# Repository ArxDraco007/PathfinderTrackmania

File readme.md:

## Building a custom wireless TrackMania controller from scratch.

## Why did I make this project?
I started this as a cool starter project to test my understanding of hardware and electronics.
I wanted to make a controller solely dedicated to a game that is customizable and fully functional with the game. I chose TrackMania, it stuck to my heart, and I made this controller.
It is a split controller to make it ergonomic and handleable to play.

## Why does my project do?
It has movement and custom buttons, such as ak40, ak60, and ak80, which, when placed in calculated best locations, provide digital steering. On a keyboard, your keys are either "on" (100% steering) or "off" (0%). However, at high speeds or on certain surfaces, 100% steering can cause the car to slide out, lose grip, or slow down. Action Keys act like a limiter or a "virtual steering wheel" that holds the wheels at a precise angle.

## Zine - 

## PICTURES - 

## Assembly Instructions?
Heat-press the brass inserts into the case and glue the magnets into place.
Screw the stabilizers into the PCB and mount the sliding switch to the case.
Solder the diodes and header pins to the Seeeduino and PCB.
Click switches into the plate, screw the plate to the case, and add keycaps.
Flash your ZMK firmware to the Seeeduino.
Repeat for the second half, pair them, and test your work.

## How to use it?
Just look at the control buttons and start playing! The WASD keys are on the left of the board, which correspond to the gas, left, brake, and right. The checkpoint and the reset buttons are below, and the AK40, AK60, and AK80 buttons, which control the full speed to 40, 60, and 80 percent. The AK60 is on the left. The AK40 and AK80 are on the right.

### BOM

| Name               | Purpose                                  | Quantity | Total Cost (USD) | Link | Distributor |
|:-------------------|:-----------------------------------------|---------:|-----------------:|:-----|:------------|
| Custom PCB         | The PCB to hold all the components       | 10  | 7.00             | [Link](https://jlcpcb.com) | JLCPCB      |
| Blank DSA Keycaps  | Keycaps on top of the cherry mx          | 10       | 5.00             | [Link](https://meckeys.com/shop/accessories/keyboard-accessories/keycaps/blank-dsa-keycaps-1u/?srsltid=AfmBOoqZibFxneEDhpmnPoNkazQzsWt6AGt-IesHtl4qNnuvjoOs5HlY-7k) | meckeys |
| Cherry MX          | The keys for the pathfinder              | 1        | 5.00             | [Link](https://meckeys.com/shop/accessories/keyboard-accessories/key-switches/cherry-mx-rgb-switch/?srsltid=AfmBOorZoRj9h-qKXHVTCJLx7y5u4I8F4N70GPuj3bCzxEowvKHzzbSTq7I) | meckeys |
| SEEED XIAO RP2040  | The main board                           | 1        | 8.00             | [Link](https://robocraze.com/products/seeed-studio-xiao-rp2040-development-board?variant=47742255562976&country=IN&currency=INR&utm_medium=product_sync&utm_source=google&utm_content=sag_organic&utm_campaign=sag_organic&campaignid=23145906364&adgroupid=182236965810&keyword=&device=c&gad_source=1&gad_campaignid=23145906364&gbraid=0AAAAADgHQvZxlmp75q0W2JPaoE08GQ6we&gclid=Cj0KCQjwkYLPBhC3ARIsAIyHi3RSv8Y8s1jQFTQlRZ37opL-OW7Et0RKjRxRr56ogXQ1huokKAxQ5zoaAn2REALw_wcB) | Robocraze |
| **1.5V LED Bulbs** | Indication of Power and Drift. | 2 | 1 | [Link](https://www.amazon.in/UNIVERSAL-Multicolour-Yellow-Pieces-3v-3-2v/dp/B09RQRP81V/) | Amazon |
| M3x4 mm Brass Heat Set Threaded Round Insert Nut (25Pcs) | Metal screw threads to hold the plastic | 1 Pack | $4.00 | [View Product](https://robu.in/product/m3-x-4-mm-brass-heat-set-knurl-threaded-round-insert-nut-25-pcs/) | Robu |
| Total | | | 30.00 | | |

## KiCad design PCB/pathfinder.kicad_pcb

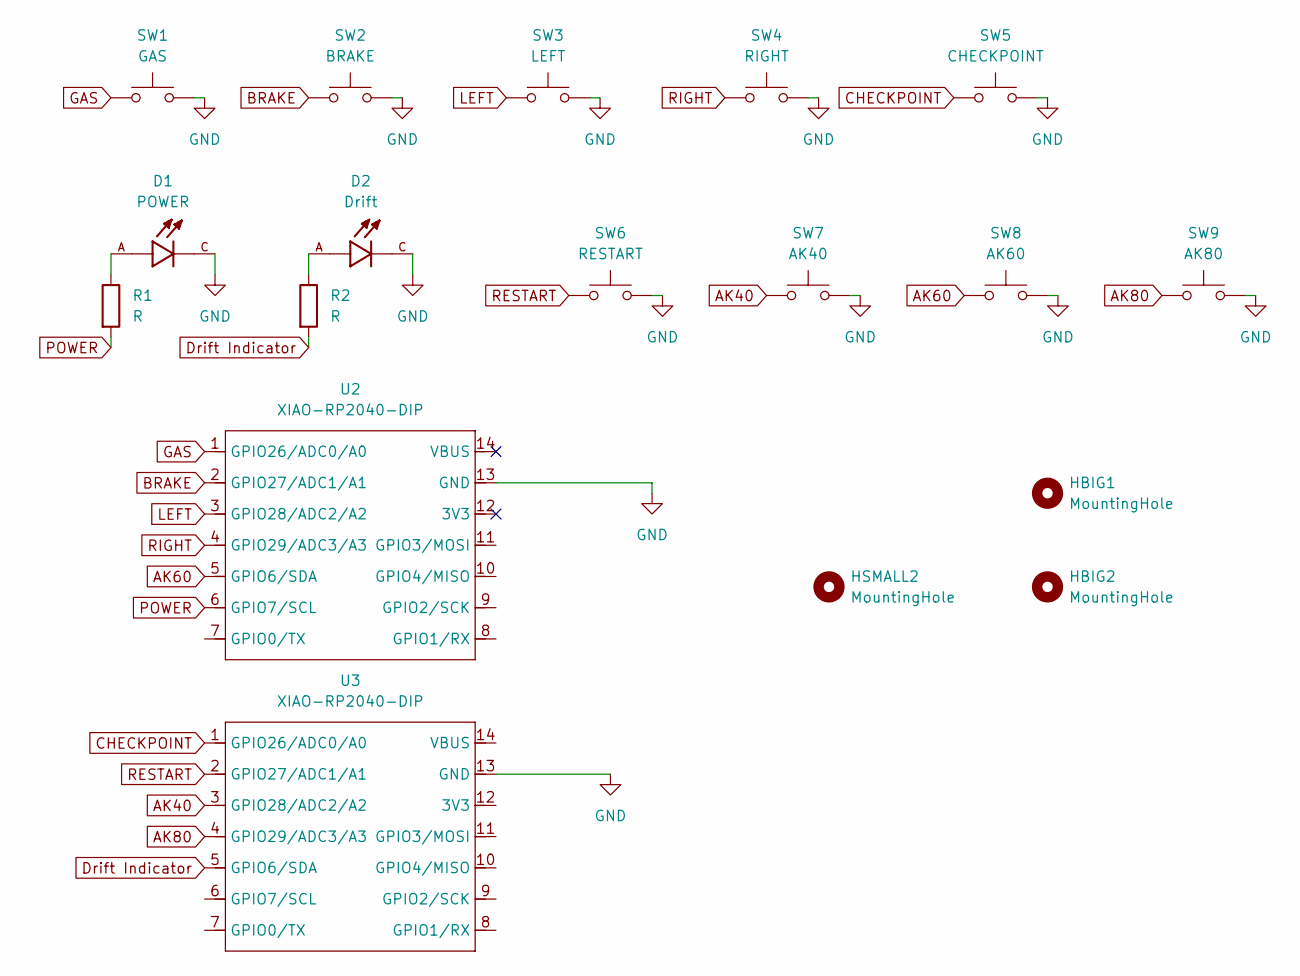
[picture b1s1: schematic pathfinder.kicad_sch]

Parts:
D1: POWER; LEDRD254W57D500H1070; PARTREV NA
D2: Drift; LEDRD254W57D500H1070; PARTREV NA
HBIG1, HBIG2: MountingHole; MountingHole_3.2mm_M3
HSMALL2: MountingHole; mouse-bite-2mm-slot
R1, R2: R; R_Axial_DIN0204_L3.6mm_D1.6mm_P5.08mm_Horizontal
SW1: GAS; SW_Cherry_MX_1.00u_PCB
SW2: BRAKE; SW_Cherry_MX_1.00u_PCB
SW3: LEFT; SW_Cherry_MX_1.00u_PCB
SW4: RIGHT; SW_Cherry_MX_1.00u_PCB
SW5: CHECKPOINT; SW_Cherry_MX_1.00u_PCB
SW6: RESTART; SW_Cherry_MX_1.00u_PCB
SW7: AK40; SW_Cherry_MX_1.00u_PCB
SW8: AK60; SW_Cherry_MX_1.00u_PCB
SW9: AK80; SW_Cherry_MX_1.00u_PCB
U2, U3: XIAO-RP2040-DIP; XIAO-Generic-Hybrid-14P-2.54-21X17.8MM

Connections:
AK40: SW7.1, U3.3 (GPIO28/ADC2/A2)
AK60: SW8.1, U2.5 (GPIO6/SDA)
AK80: SW9.1, U3.4 (GPIO29/ADC3/A3)
BRAKE: SW2.1, U2.2 (GPIO27/ADC1/A1)
CHECKPOINT: SW5.1, U3.1 (GPIO26/ADC0/A0)
Drift Indicator: R2.2, U3.5 (GPIO6/SDA)
GAS: SW1.1, U2.1 (GPIO26/ADC0/A0)
GND: D1.C, D2.C, SW1.2, SW2.2, SW3.2, SW4.2, SW5.2, SW6.2, SW7.2, SW8.2, SW9.2, U2.13 (GND), U3.13 (GND)
LEFT: SW3.1, U2.3 (GPIO28/ADC2/A2)
unnamed: D1.A, R1.1
unnamed: D2.A, R2.1
POWER: R1.2, U2.6 (GPIO7/SCL)
RESTART: SW6.1, U3.2 (GPIO27/ADC1/A1)
RIGHT: SW4.1, U2.4 (GPIO29/ADC3/A3)

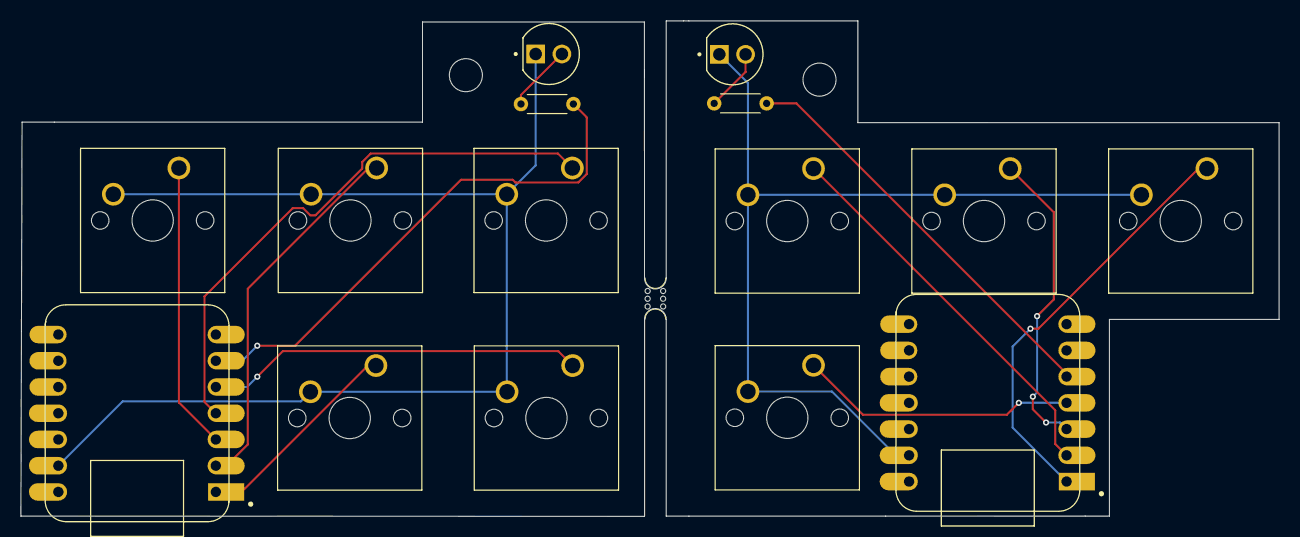
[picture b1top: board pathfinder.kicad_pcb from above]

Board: 2 copper layers, 121.8 x 48.0 mm, 18 parts (0 on the bottom side), 14 nets.

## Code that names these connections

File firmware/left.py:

import board
import digitalio
import usb_hid
import keypad
from adafruit_hid.keyboard import Keyboard
from adafruit_hid.keycode import Keycode

kbd = Keyboard(usb_hid.devices)

BUTTON_PINS = (
    board.D0,  # GAS    - GPIO26/A0
    board.D1,  # BRAKE  - GPIO27/A1
    board.D2,  # LEFT   - GPIO28/A2
    board.D3,  # RIGHT  - GPIO29/A3
    board.D4,  # AK60   - GPIO6/SDA
    board.D5,  # POWER  - GPIO7/SCL
)

KEYCODES = (
    Keycode.UP_ARROW,    # GAS
    Keycode.DOWN_ARROW,  # BRAKE
    Keycode.LEFT_ARROW,  # LEFT
    Keycode.RIGHT_ARROW, # RIGHT
    Keycode.THREE,       # AK60
    Keycode.ONE,         # POWER (set to your needed key)
)

keys = keypad.Keys(BUTTON_PINS, value_when_pressed=False, pull=True)

# POWER LED - always on, using a spare pin (e.g. D6 = GPIO3/MOSI on U2)
power_led = digitalio.DigitalInOut(board.D6)
power_led.direction = digitalio.Direction.OUTPUT
power_led.value = True

while True:
    event = keys.events.get()

    if event:
        key_idx = event.key_number

        if event.pressed:
            kbd.press(KEYCODES[key_idx])

        if event.released:
            kbd.release(KEYCODES[key_idx])

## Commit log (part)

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2026-04-17 PCB Design
    PCB Design
2026-04-17 Initialize README with project information
    Added project overview, pictures, and BOM details.
2026-05-01 Adding the Zine
2026-05-01 Revise readme to include project usage and features
    Added details about project functionality and usage.
2026-05-02 changes!!!!
2026-06-01 Updates CAD
2026-06-04 Production Files
2026-06-04 assembly
2026-06-04 step files
2026-06-04 zineing
2026-06-04 gerber and drill
2026-06-05 Revise readme with project details and images
    Updated the readme to include additional images and details about the project.
2026-06-05 zine change
2026-06-05 CAD Changes
2026-06-08 pcb change
2026-06-08 rotated the xiao
2026-06-08 fusion acc to kicad
2026-06-08 removal of backups
2026-06-11 gerbrrr
2026-06-11 remove
2026-06-12 gerber and pcb
2026-06-12 zine
2026-06-12 firmware update
2026-06-16 Revise readme with assembly instructions and images
    Updated the readme to include assembly instructions and additional images.
2026-06-16 prod, cad,
